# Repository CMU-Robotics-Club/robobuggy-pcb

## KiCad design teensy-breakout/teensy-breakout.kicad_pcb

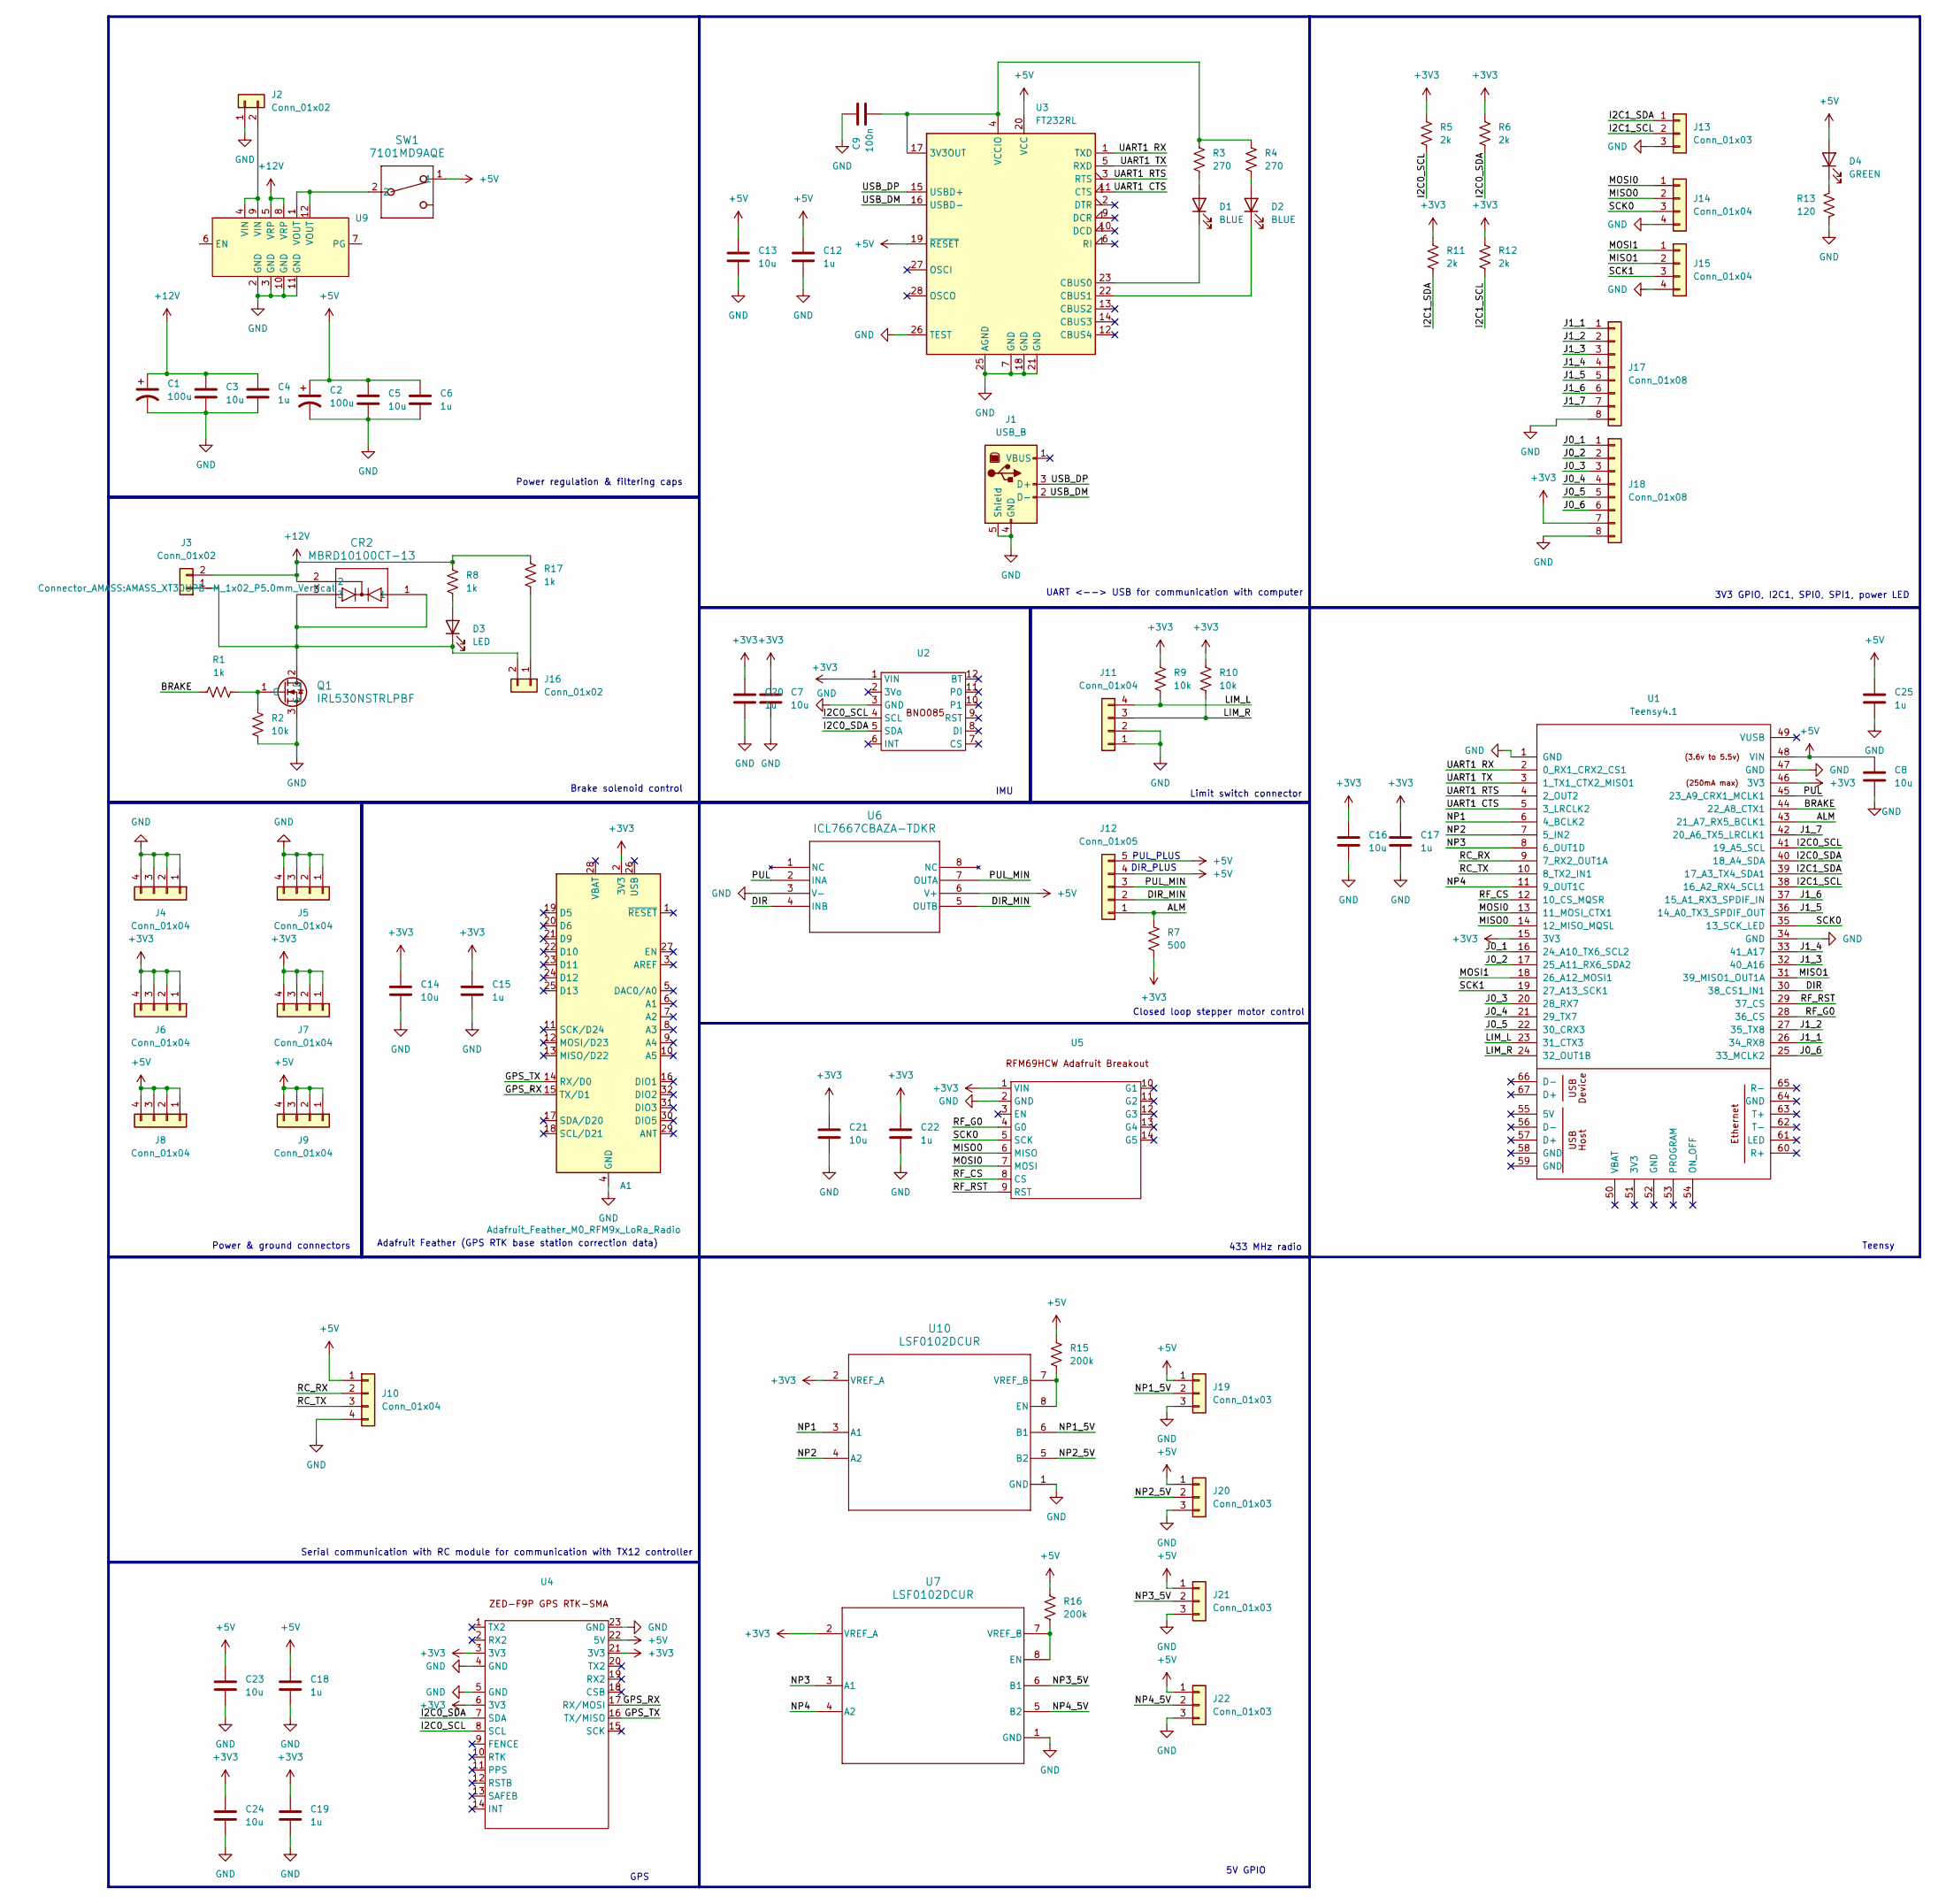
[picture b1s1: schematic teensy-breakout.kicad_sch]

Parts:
A1: Adafruit_Feather_M0_RFM9x_LoRa_Radio; Adafruit_Feather_M0_RFM
C1, C2: 100u; CAP_A765EB_KEM
C3, C5, C7, C8, C13, C14, C16, C21, C23, C24: 10u; C_0805_2012Metric_Pad1.18x1.45mm_HandSolder
C4, C6, C12, C15, C17, C18, C19, C20, C22, C25: 1u; C_0805_2012Metric_Pad1.18x1.45mm_HandSolder
C9: 100n; C_0805_2012Metric_Pad1.18x1.45mm_HandSolder
CR2: MBRD10100CT-13; TO252DPAK_DIO
D1, D2: BLUE; LED_0805_2012Metric
D3: LED; LED_0805_2012Metric_Pad1.15x1.40mm_HandSolder
D4: GREEN; LED_0805_2012Metric
J1: USB_B; USB_B_OST_USB-B1HSxx_Horizontal
J2, J3: Conn_01x02; AMASS_XT30UPB-M_1x02_P5.0mm_Vertical
J4, J5, J6, J7, J8, J9, J10, J11, J14, J15: Conn_01x04; JST_EH_B4B-EH-A_1x04_P2.50mm_Vertical
J12: Conn_01x05; JST_EH_B5B-EH-A_1x05_P2.50mm_Vertical
J13, J19, J20, J21, J22: Conn_01x03; JST_EH_B3B-EH-A_1x03_P2.50mm_Vertical
J16: Conn_01x02; JST_EH_B2B-EH-A_1x02_P2.50mm_Vertical
J17, J18: Conn_01x08; PHOENIX_1989010
Q1: IRL530NSTRLPBF; IRL530NSTRLPBF_INF
R1: 1k; R_0805_2012Metric
R2: 10k; R_0805_2012Metric
R3, R4: 270; R_0805_2012Metric_Pad1.20x1.40mm_HandSolder
R5, R6, R11, R12: 2k; R_0805_2012Metric_Pad1.20x1.40mm_HandSolder
R7: 500; R_0805_2012Metric_Pad1.20x1.40mm_HandSolder
R8, R17: 1k; R_0805_2012Metric_Pad1.20x1.40mm_HandSolder
R9, R10: 10k; R_0805_2012Metric_Pad1.20x1.40mm_HandSolder
R13: 120; R_0805_2012Metric_Pad1.20x1.40mm_HandSolder
R15, R16: 200k; R_0805_2012Metric_Pad1.20x1.40mm_HandSolder
SW1: 7101MD9AQE; SW3_7101MD9AQE_CNK
U1: Teensy4.1; Teensy41
U2: BNO085
U3: FT232RL; SSOP-28_5.3x10.2mm_P0.65mm
U4: ZED F9P RTK SMA
U5: RFM69HCW Adafruit Breakout
U6: ICL7667CBAZA-TDKR; SOIC8_4X5_INR
U7, U10: LSF0102DCUR; DCU0008A_M
U9: Pololu D36V50F5

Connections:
+3V3: A1.2 (3V3), C7.1, C14.1, C15.2, C16.1, C17.2, C19.1, C20.1, C21.1, C22.1, C24.1, J6.1, J6.2, J6.3, J6.4, J7.1, J7.2, J7.3, J7.4, J18.7, R5.1, R6.1, R7.2, R9.1, R10.1, R11.1, R12.1, U1.15 (3V3), U1.46 (3V3), U2.1 (VIN), U4.3 (3V3), U4.6 (3V3), U4.21 (3V3), U5.1 (VIN), U7.2 (VREF_A), U10.2 (VREF_A)
+5V: C2.1, C5.1, C6.1, C8.1, C12.1, C13.1, C18.1, C23.1, C25.1, D4.2 (A), J8.1, J8.2, J8.3, J8.4, J9.1, J9.2, J9.3, J9.4, J10.1, J12.4, J12.5, J19.1, J20.1, J21.1, J22.1, R15.1, R16.1, SW1.1, U1.48 (VIN), U3.19 (~RESET), U3.20 (VCC), U4.22 (5V), U6.6 (V+)
+12V: C1.1, C3.1, C4.1, CR2.2, J3.2, R8.1, R17.1, U9.5 (VRP), U9.8 (VRP)
/ALM: J12.1, R7.1, U1.43 (21_A7_RX5_BCLK1)
/BRAKE: R1.1, U1.44 (22_A8_CTX1)
/DIR: U1.30 (38_CS1_IN1), U6.4 (INB)
/DIR_MIN: J12.2, U6.5 (OUTB)
/GPS_RX: A1.15 (TX/D1), U4.17 (RX/MOSI)
/GPS_TX: A1.14 (RX/D0), U4.16 (TX/MISO)
/I2C0_SCL: R5.2, U1.41 (19_A5_SCL), U2.4 (SCL), U4.8 (SCL)
/I2C0_SDA: R6.2, U1.40 (18_A4_SDA), U2.5 (SDA), U4.7 (SDA)
/I2C1_SCL: J13.2, R12.2, U1.38 (16_A2_RX4_SCL1)
/I2C1_SDA: J13.1, R11.2, U1.39 (17_A3_TX4_SDA1)
/J0_1: J18.1, U1.16 (24_A10_TX6_SCL2)
/J0_2: J18.2, U1.17 (25_A11_RX6_SDA2)
/J0_3: J18.3, U1.20 (28_RX7)
/J0_4: J18.4, U1.21 (29_TX7)
/J0_5: J18.5, U1.22 (30_CRX3)
/J0_6: J18.6, U1.25 (33_MCLK2)
/J1_1: J17.1, U1.26 (34_RX8)
/J1_2: J17.2, U1.27 (35_TX8)
/J1_3: J17.3, U1.32 (40_A16)
/J1_4: J17.4, U1.33 (41_A17)
/J1_5: J17.5, U1.36 (14_A0_TX3_SPDIF_OUT)
/J1_6: J17.6, U1.37 (15_A1_RX3_SPDIF_IN)
/J1_7: J17.7, U1.42 (20_A6_TX5_LRCLK1)
/LIM_L: J11.4, R9.2, U1.23 (31_CTX3)
/LIM_R: J11.3, R10.2, U1.24 (32_OUT1B)
/MISO0: J14.2, U1.14 (12_MISO_MQSL), U5.6 (MISO)
/MISO1: J15.2, U1.31 (39_MISO1_OUT1A)
/MOSI0: J14.1, U1.13 (11_MOSI_CTX1), U5.7 (MOSI)
/MOSI1: J15.1, U1.18 (26_A12_MOSI1)
/NP1: U1.6 (4_BCLK2), U10.3 (A1)
/NP1_5V: J19.2, U10.6 (B1)
/NP2: U1.7 (5_IN2), U10.4 (A2)
/NP2_5V: J20.2, U10.5 (B2)
/NP3: U1.8 (6_OUT1D), U7.3 (A1)
/NP3_5V: J21.2, U7.6 (B1)
/NP4: U1.11 (9_OUT1C), U7.4 (A2)
/NP4_5V: J22.2, U7.5 (B2)
/PUL: U1.45 (23_A9_CRX1_MCLK1), U6.2 (INA)
/PUL_MIN: J12.3, U6.7 (OUTA)
/RC_RX: J10.2, U1.9 (7_RX2_OUT1A)
/RC_TX: J10.3, U1.10 (8_TX2_IN1)
/RF_CS: U1.12 (10_CS_MQSR), U5.8 (CS)
/RF_G0: U1.28 (36_CS), U5.4 (G0)
/RF_RST: U1.29 (37_CS), U5.9 (RST)
/SCK0: J14.3, U1.35 (13_SCK_LED), U5.5 (SCK)
/SCK1: J15.3, U1.19 (27_A13_SCK1)
/UART1 CTS: U1.5 (3_LRCLK2), U3.11 (CTS)
/UART1 RTS: U1.4 (2_OUT2), U3.3 (RTS)
/UART1 RX: U1.2 (0_RX1_CRX2_CS1), U3.1 (TXD)
/UART1 TX: U1.3 (1_TX1_CTX2_MISO1), U3.5 (RXD)
/USB_DM: J1.2 (D-), U3.16 (USBD-)
/USB_DP: J1.3 (D+), U3.15 (USBD+)
GND: A1.4 (GND), C1.2, C2.2, C3.2, C4.2, C5.2, C6.2, C7.2, C8.2, C9.1, C12.2, C13.2, C14.2, C15.1, C16.2, C17.1, C18.2, C19.2, C20.2, C21.2, C22.2, C23.2, C24.2, C25.2, J1.4 (GND), J1.5 (Shield), J2.1, J4.1, J4.2, J4.3, J4.4, J5.1, J5.2, J5.3, J5.4, J10.4, J11.1, J11.2, J13.3, J14.4, J15.4, J17.8, J18.8, J19.3, J20.3, J21.3, J22.3, Q1.3 (S), R2.1, R13.2, U1.1 (GND), U1.34 (GND), U1.47 (GND), U2.3 (GND), U3.7 (GND), U3.18 (GND), U3.21 (GND), U3.25 (AGND), U3.26 (TEST), U4.4 (GND), U4.5 (GND), U4.23 (GND), U5.2 (GND), U6.3 (V-), U7.1 (GND), U9.2 (GND), U9.3 (GND), U9.10 (GND), U9.11 (GND), U10.1 (GND)
unnamed: D1.2 (A), R3.2
unnamed: D1.1 (K), U3.23 (CBUS0)
unnamed: D2.2 (A), R4.2
unnamed: D2.1 (K), U3.22 (CBUS1)
unnamed: D3.2 (A), R8.2
unnamed: CR2.1, CR2.3, D3.1 (K), J3.1, J16.2, Q1.2 (D)
unnamed: D4.1 (K), R13.1
unnamed: J2.2, U9.4 (VIN), U9.9 (VIN)
unnamed: J16.1, R17.2
unnamed: Q1.1 (G), R1.2, R2.2
unnamed: SW1.2, U9.1 (VOUT), U9.12 (VOUT)
unnamed: C9.2, R3.1, R4.1, U3.4 (VCCIO), U3.17 (3V3OUT)
unnamed: R16.2, U7.7 (VREF_B), U7.8 (EN)
unnamed: R15.2, U10.7 (VREF_B), U10.8 (EN)

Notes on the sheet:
Brake solenoid control
UART <--> USB for communication with computer
IMU
5V GPIO
Teensy
PUL_PLUS
3V3 GPIO, I2C1, SPI0, SPI1, power LED
Closed loop stepper motor control
Power regulation & filtering caps
Limit switch connector
DIR_PLUS
433 MHz radio
Adafruit Feather (GPS RTK base station correction data)
GPS
Serial communication with RC module for communication with TX12 controller
Power & ground connectors

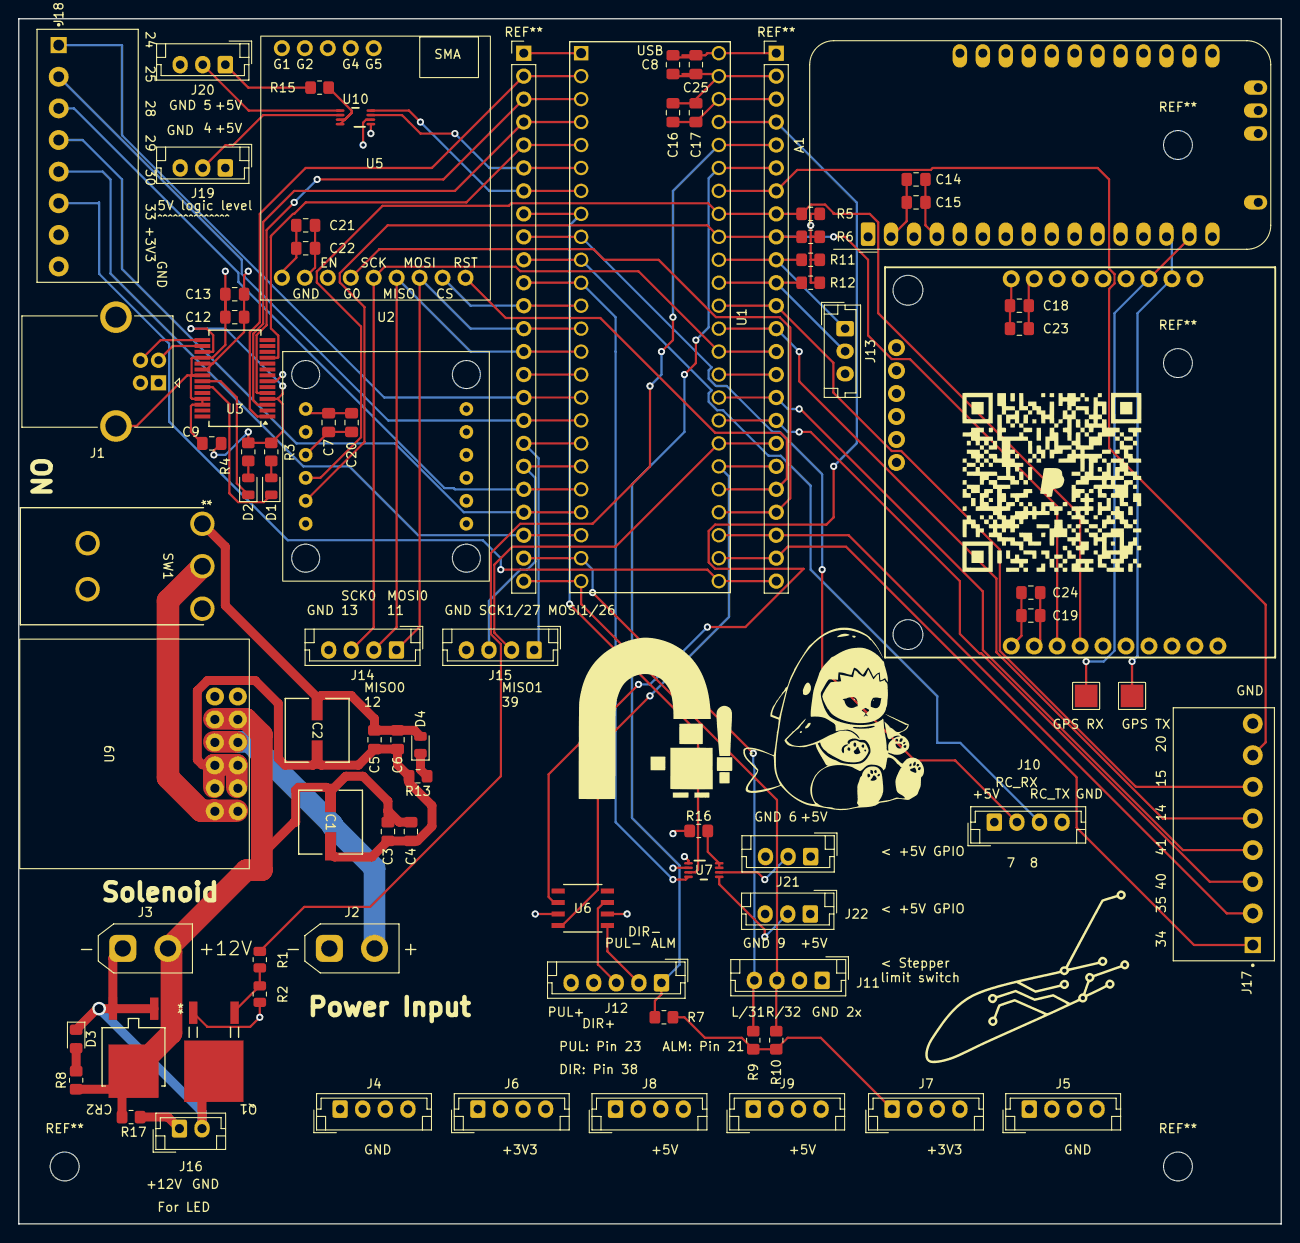
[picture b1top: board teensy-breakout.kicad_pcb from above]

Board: 6 copper layers, 139.7 x 133.4 mm, 78 parts (0 on the bottom side), 70 nets.

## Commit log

2024-12-14 initial commit for teensy breakout
2024-12-15 Initial work on teensy brakeout PCB
2024-12-19 Started working to integrate ZED-F9P and feather. Still need to make Zed-F9P footprint.
2024-12-29 More work done on schematic, seems good to me
2024-12-29 Forgot to add power LED
2025-01-10 Work on layout & wiring. Mostly done, need to look it over. It's very messy :(
2025-01-10 Added connection for limit switches, started work on adding headers
2025-01-10 Fixed limit switch connection
2025-01-11 Final commit before meeting
2025-01-14 Updated power via sizes to ensure meeting power requirements
2025-01-15 Final silkscreen & testpoint touchups (still no images tho)
2025-01-15 Changed mounting holes to use included M3 size
2025-01-16 Improved schematic layout, still in progress
2025-01-16 Addde initial gitignore
2025-01-16 Added text description to each of the boxes
2025-01-16 Updated gitignore
2025-01-16 Updated symbol library table to remove unnecessary & non-present libraries
2025-01-22 Added footprints for connectors. Mostly JST, some XT30 and screw terminals.
2025-01-28 Did most of the routing, need to add pinouts and mounting holes
2025-02-02 Added most of the silkscreen
2025-02-02 Added rest of silkscreen
2025-02-02 Fixed DRC warnings
2025-02-02 Fix small issue
2025-02-02 Did I forget to save last time?
